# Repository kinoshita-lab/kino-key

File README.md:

# Kino-Key25

[日本語](README.ja.md)

Open source piano-type keyboard MIDI controller project

## Features

- All mechanical parts are easy 3D-printable. You can also easly order to 3D printing manufactures, such as JLC3dP, etc. (we may sell mech parts in the future, but not planned)
- Software is implemented on small, cheap seeeduino xiao rp2040. Everything includes keyboard scanning is modifiable according to your preferences.
- Most of the components on the PCB is easy to buy(we may sell PCBA board for easier assembly in the future, but not planned)

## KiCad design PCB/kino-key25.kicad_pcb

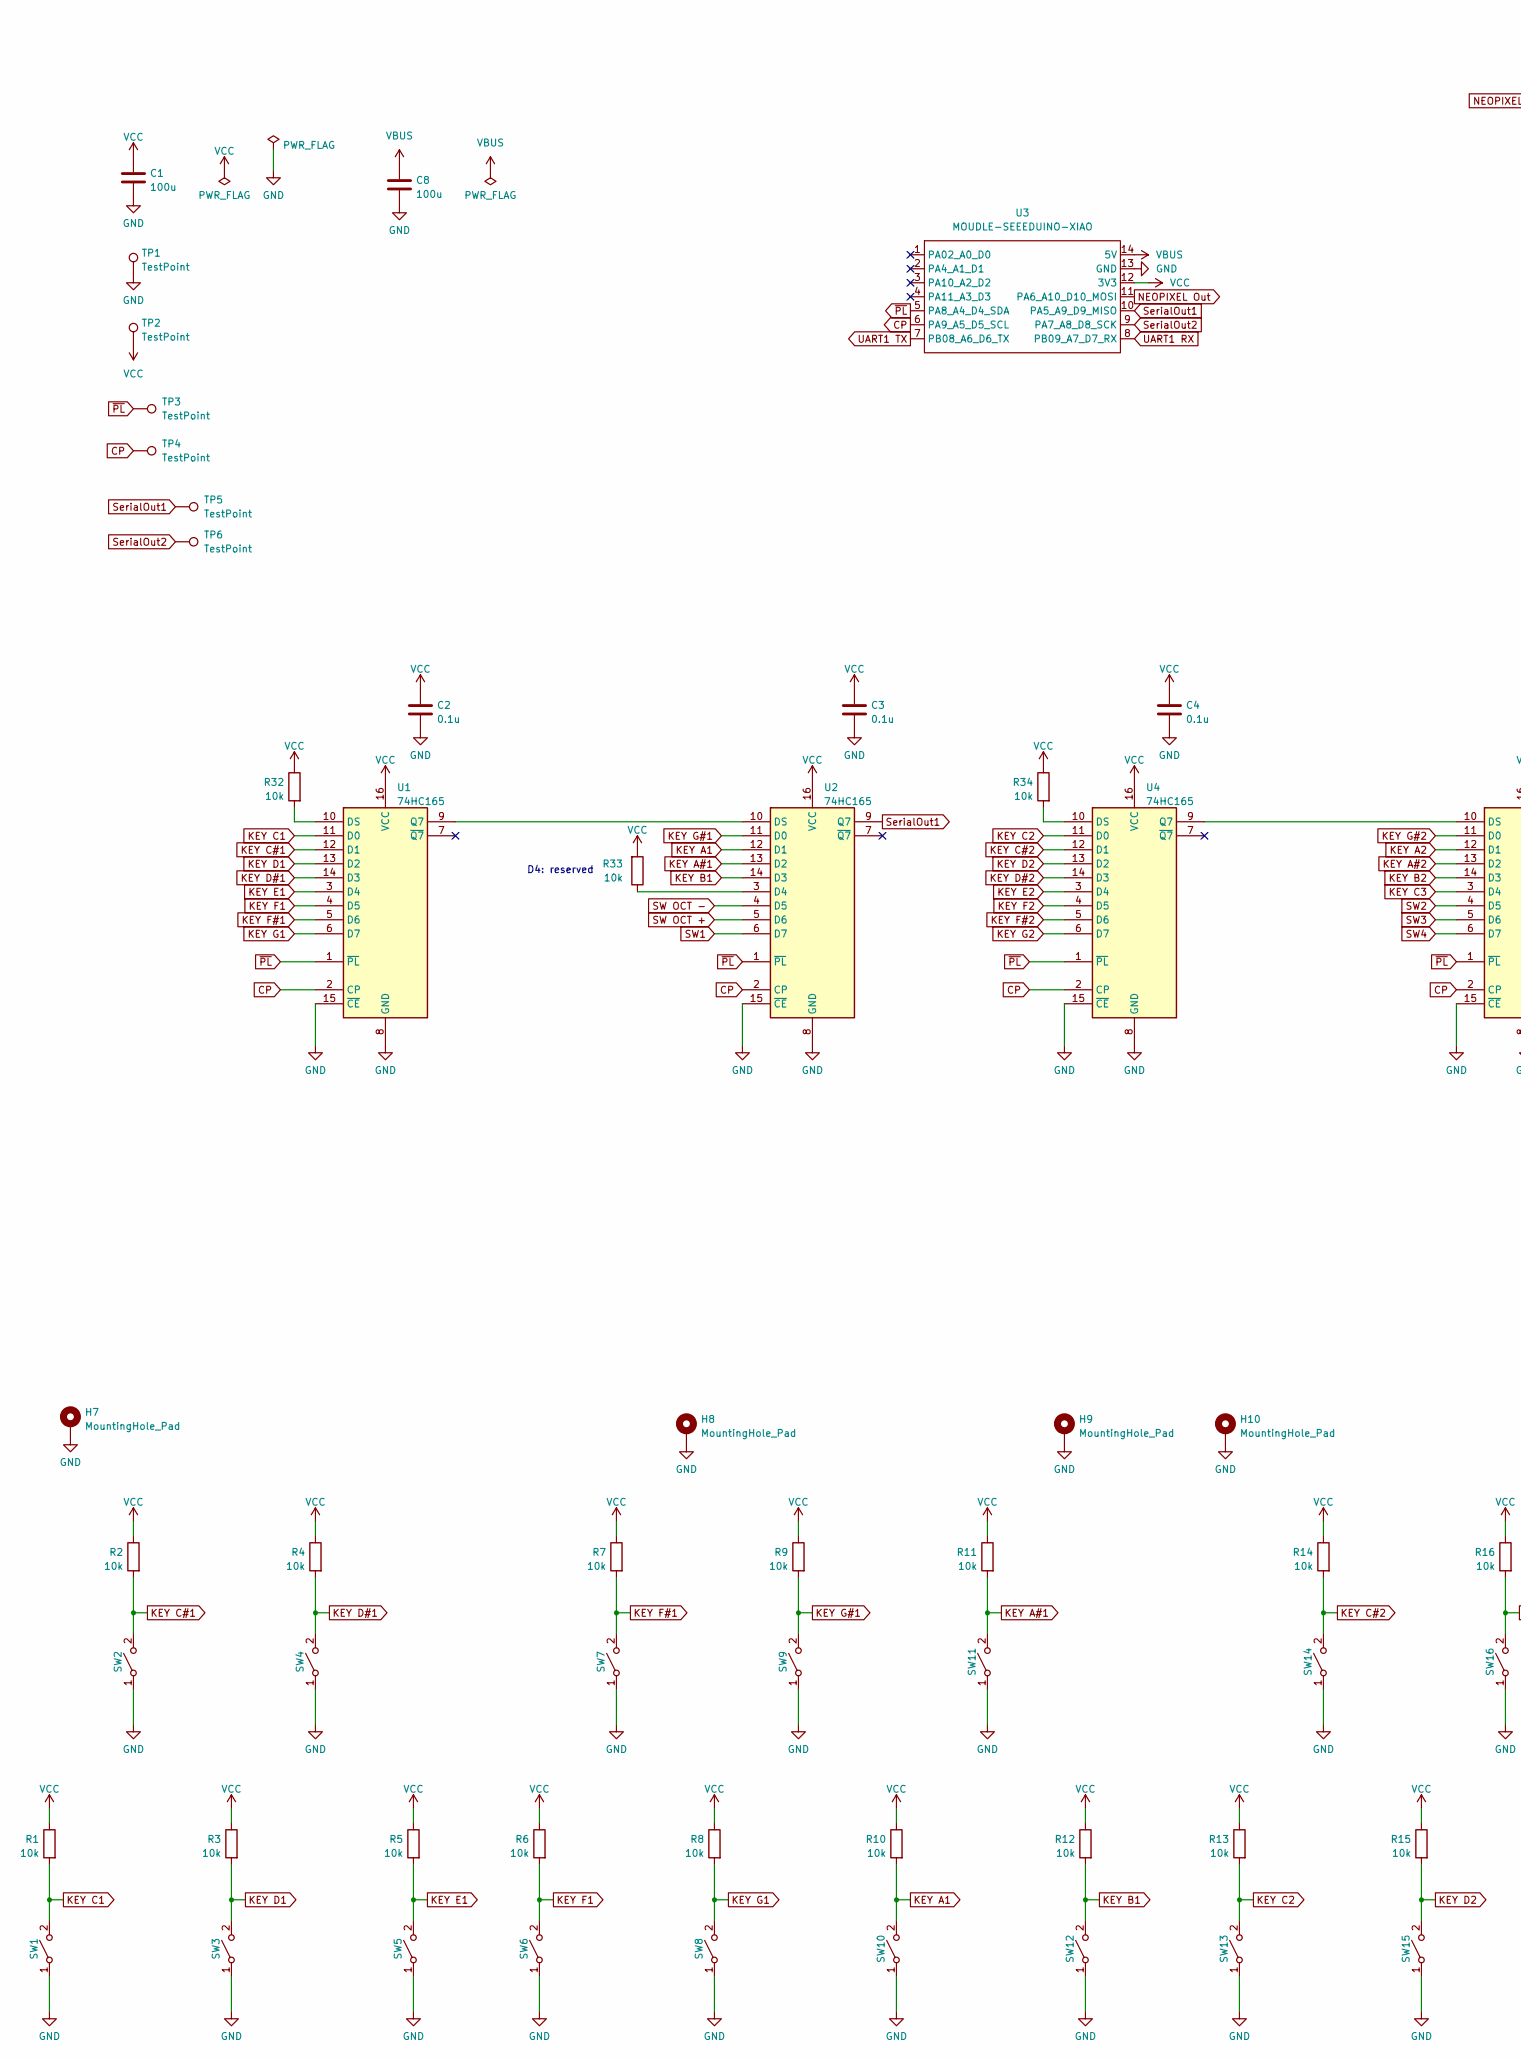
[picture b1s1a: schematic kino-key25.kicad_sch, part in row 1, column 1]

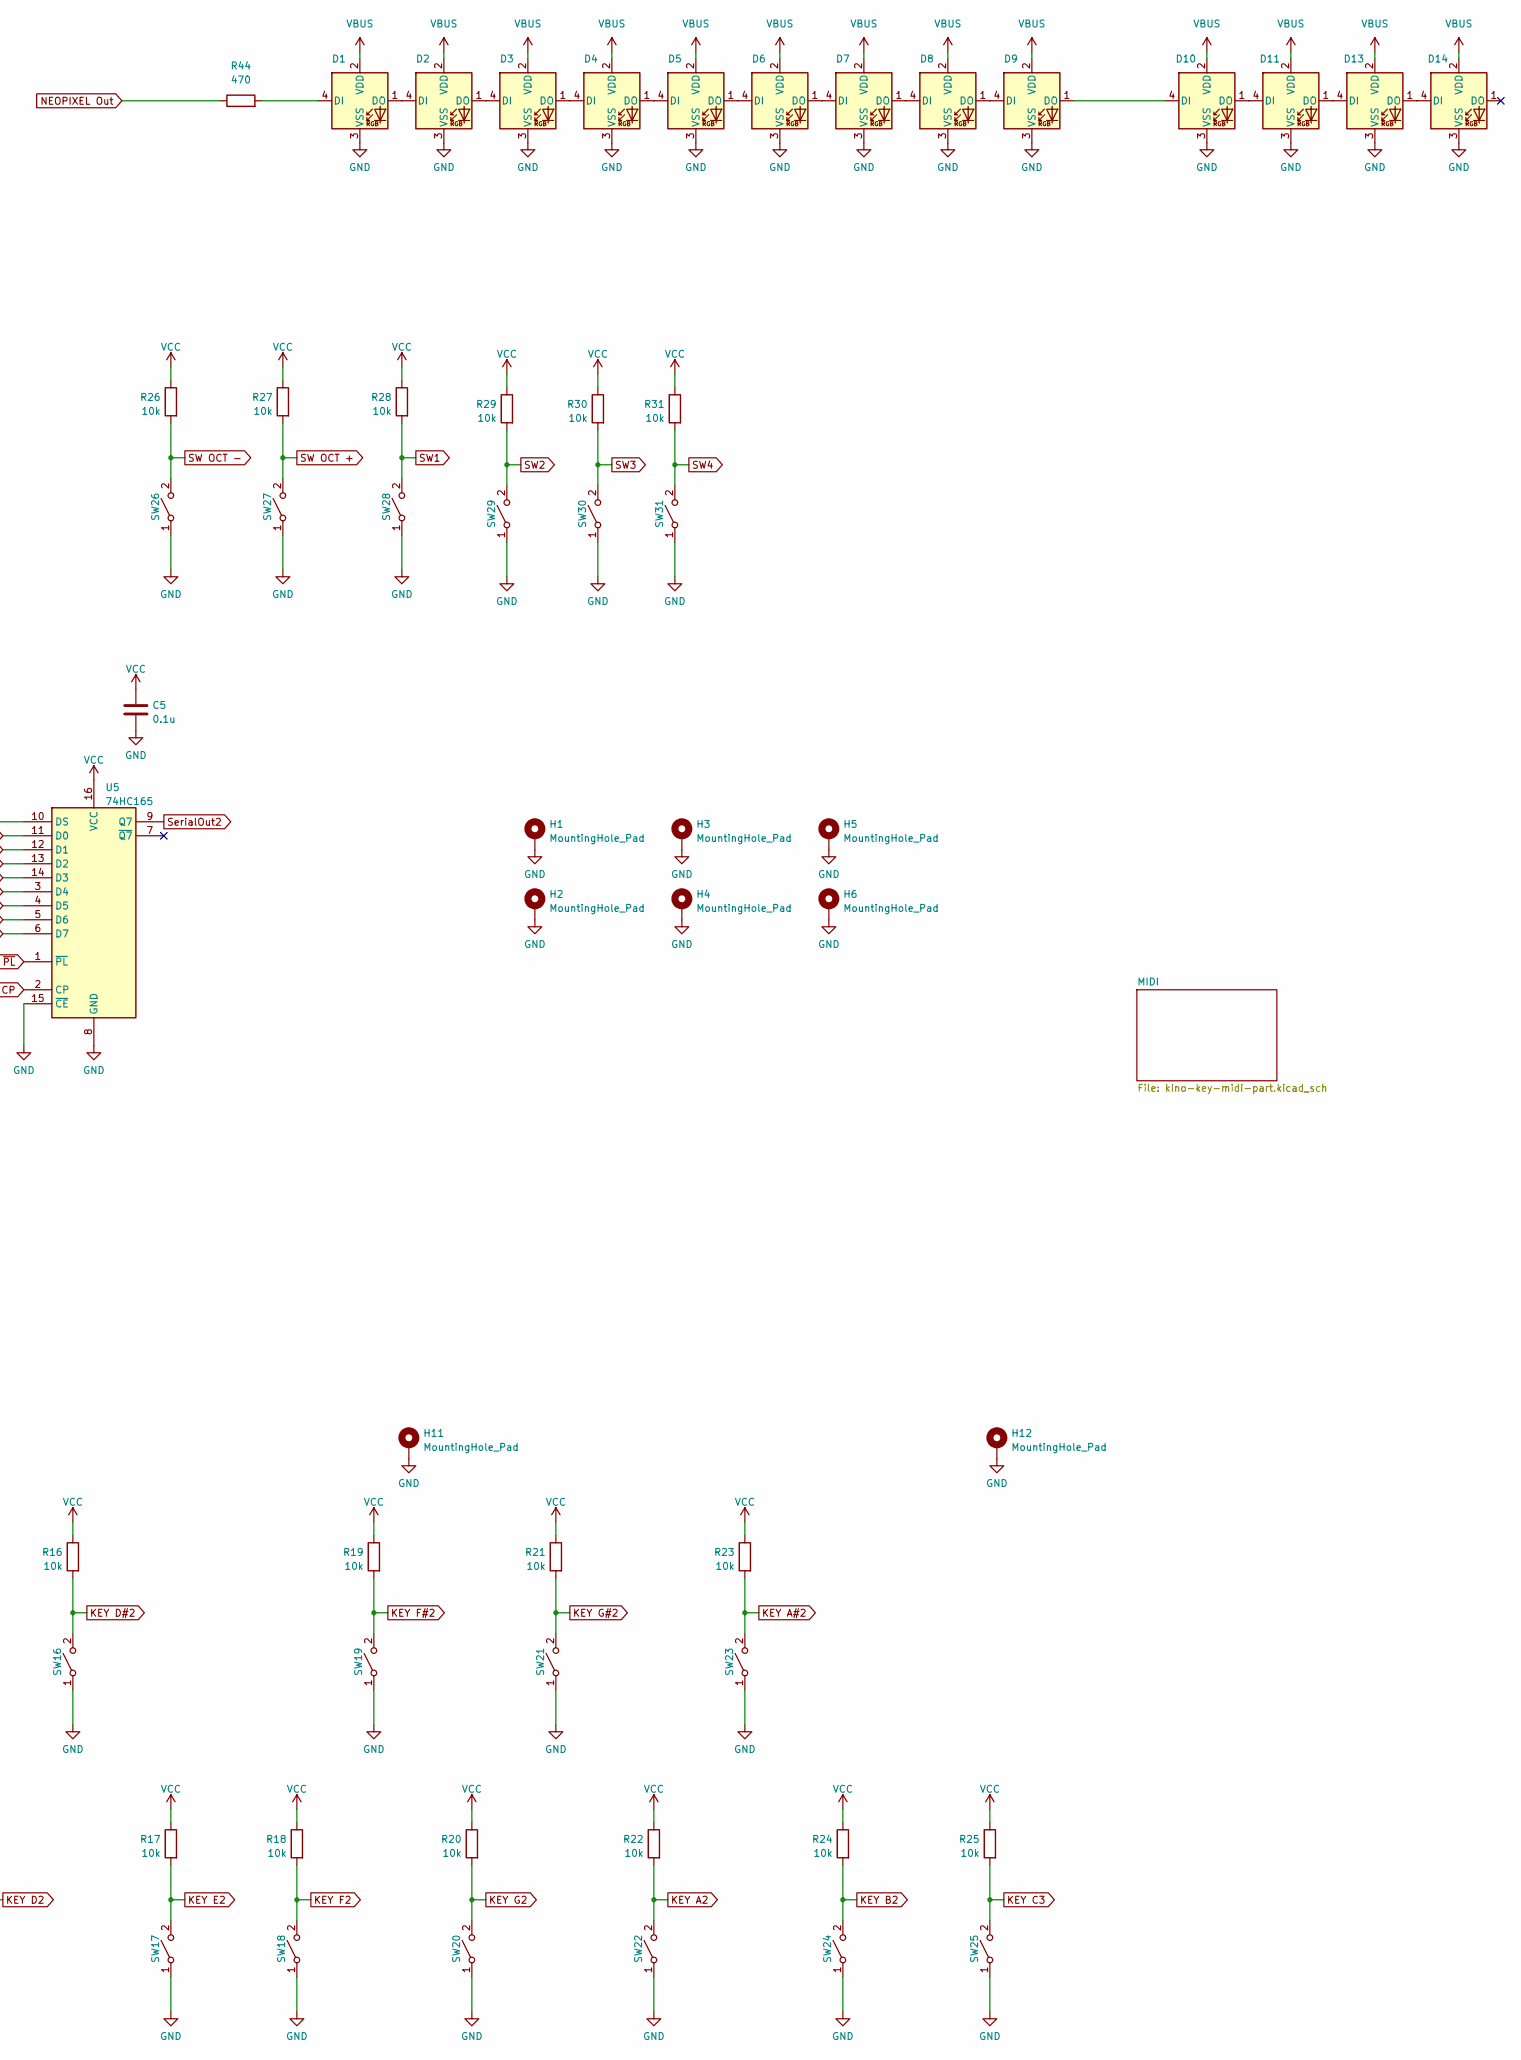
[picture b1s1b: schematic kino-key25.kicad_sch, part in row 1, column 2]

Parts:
C1, C8: 100u; C_1206_3216Metric_Pad1.33x1.80mm_HandSolder; LCSC C312983
C2, C3, C4, C5: 0.1u; C_0402_1005Metric_Pad0.74x0.62mm_HandSolder; LCSC C1525
D1, D2, D3, D4, D5, D6, D7, D8, D9, D10, D11, D13, D14: LED_NeoPixel_XL-1615RGBC-WS2812B; LCSC C5349954
H1, H2, H3, H4, H5, H6, H7, H8, H9, H10, H11, H12: MountingHole_Pad; MountingHole_3.2mm_M3_DIN965_Pad
R1, R2, R3, R4, R5, R6, R7, R8, R9, R10, R11, R12, R13, R14, R15, R16, R17, R18, R19, R20, R21, R22, R23, R24, R25, R26, R27, R28, R29, R30, R31, R32, R33, R34: 10k; R_0402_1005Metric_Pad0.72x0.64mm_HandSolder; LCSC C25744
R44: 470; R_0603_1608Metric; LCSC C23179
SW1, SW2, SW3, SW4, SW5, SW6, SW7, SW8, SW9, SW10, SW11, SW12, SW13, SW14, SW15, SW16, SW17, SW18, SW19, SW20, SW21, SW22, SW23, SW24, SW25, SW26, SW27, SW28, SW29, SW30, SW31: SW_SPST; SW_Tactile_6mm_x_6mm_Futsuuno_SMD; LCSC C294566
TP1, TP2, TP3, TP4, TP5, TP6: TestPoint; TestPoint_THTPad_D2.0mm_Drill1.0mm
U1, U2, U4, U5: 74HC165; TSSOP-16_4.4x5mm_P0.65mm; LCSC C80696
U3: MOUDLE-SEEEDUINO-XIAO; Seeduino_Xiao_RP2040_MOUDLE14P-2.54-21X17.8MM

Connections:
CP: TP4.1, U1.2 (CP), U2.2 (CP), U3.6 (PA9_A5_D5_SCL), U4.2 (CP), U5.2 (CP)
GND: C1.2, C2.2, C3.2, C4.2, C5.2, C8.2, D1.3 (VSS), D2.3 (VSS), D3.3 (VSS), D4.3 (VSS), D5.3 (VSS), D6.3 (VSS), D7.3 (VSS), D8.3 (VSS), D9.3 (VSS), D10.3 (VSS), D11.3 (VSS), D13.3 (VSS), D14.3 (VSS), H1.1, H2.1, H3.1, H4.1, H5.1, H6.1, H7.1, H8.1, H9.1, H10.1, H11.1, H12.1, SW1.1 (A), SW2.1 (A), SW3.1 (A), SW4.1 (A), SW5.1 (A), SW6.1 (A), SW7.1 (A), SW8.1 (A), SW9.1 (A), SW10.1 (A), SW11.1 (A), SW12.1 (A), SW13.1 (A), SW14.1 (A), SW15.1 (A), SW16.1 (A), SW17.1 (A), SW18.1 (A), SW19.1 (A), SW20.1 (A), SW21.1 (A), SW22.1 (A), SW23.1 (A), SW24.1 (A), SW25.1 (A), SW26.1 (A), SW27.1 (A), SW28.1 (A), SW29.1 (A), SW30.1 (A), SW31.1 (A), TP1.1, U1.8 (GND), U1.15 (~CE), U2.8 (GND), U2.15 (~CE), U3.13 (GND), U4.8 (GND), U4.15 (~CE), U5.8 (GND), U5.15 (~CE); also elsewhere on the board
KEY A1: R10.2, SW10.2 (B), U2.12 (D1)
KEY A2: R22.2, SW22.2 (B), U5.12 (D1)
KEY A#1: R11.2, SW11.2 (B), U2.13 (D2)
KEY A#2: R23.2, SW23.2 (B), U5.13 (D2)
KEY B1: R12.2, SW12.2 (B), U2.14 (D3)
KEY B2: R24.2, SW24.2 (B), U5.14 (D3)
KEY C1: R1.2, SW1.2 (B), U1.11 (D0)
KEY C2: R13.2, SW13.2 (B), U4.11 (D0)
KEY C3: R25.2, SW25.2 (B), U5.3 (D4)
KEY C#1: R2.2, SW2.2 (B), U1.12 (D1)
KEY C#2: R14.2, SW14.2 (B), U4.12 (D1)
KEY D1: R3.2, SW3.2 (B), U1.13 (D2)
KEY D2: R15.2, SW15.2 (B), U4.13 (D2)
KEY D#1: R4.2, SW4.2 (B), U1.14 (D3)
KEY D#2: R16.2, SW16.2 (B), U4.14 (D3)
KEY E1: R5.2, SW5.2 (B), U1.3 (D4)
KEY E2: R17.2, SW17.2 (B), U4.3 (D4)
KEY F1: R6.2, SW6.2 (B), U1.4 (D5)
KEY F2: R18.2, SW18.2 (B), U4.4 (D5)
KEY F#1: R7.2, SW7.2 (B), U1.5 (D6)
KEY F#2: R19.2, SW19.2 (B), U4.5 (D6)
KEY G1: R8.2, SW8.2 (B), U1.6 (D7)
KEY G2: R20.2, SW20.2 (B), U4.6 (D7)
KEY G#1: R9.2, SW9.2 (B), U2.11 (D0)
KEY G#2: R21.2, SW21.2 (B), U5.11 (D0)
NEOPIXEL Out: R44.1, U3.11 (PA6_A10_D10_MOSI)
unnamed: D1.4 (DI), R44.2
unnamed: D1.1 (DO), D2.4 (DI)
unnamed: D2.1 (DO), D3.4 (DI)
unnamed: D3.1 (DO), D4.4 (DI)
unnamed: D4.1 (DO), D5.4 (DI)
unnamed: D5.1 (DO), D6.4 (DI)
unnamed: D6.1 (DO), D7.4 (DI)
unnamed: D7.1 (DO), D8.4 (DI)
unnamed: D8.1 (DO), D9.4 (DI)
unnamed: D9.1 (DO), D10.4 (DI)
unnamed: D10.1 (DO), D11.4 (DI)
unnamed: D11.1 (DO), D13.4 (DI)
unnamed: D13.1 (DO), D14.4 (DI)
unnamed: R32.2, U1.10 (DS)
unnamed: U1.9 (Q7), U2.10 (DS)
unnamed: R33.1, U2.3 (D4)
unnamed: R34.2, U4.10 (DS)
unnamed: U4.9 (Q7), U5.10 (DS)
SW1: R28.2, SW28.2 (B), U2.6 (D7)
SW2: R29.2, SW29.2 (B), U5.4 (D5)
SW3: R30.2, SW30.2 (B), U5.5 (D6)
SW4: R31.2, SW31.2 (B), U5.6 (D7)
SW OCT +: R27.2, SW27.2 (B), U2.5 (D6)
SW OCT -: R26.2, SW26.2 (B), U2.4 (D5)
SerialOut1: TP5.1, U2.9 (Q7), U3.10 (PA5_A9_D9_MISO)
SerialOut2: TP6.1, U3.9 (PA7_A8_D8_SCK), U5.9 (Q7)
UART1 RX: U3.8 (PB09_A7_D7_RX); also elsewhere on the board
UART1 TX: U3.7 (PB08_A6_D6_TX); also elsewhere on the board
VBUS: C8.1, D1.2 (VDD), D2.2 (VDD), D3.2 (VDD), D4.2 (VDD), D5.2 (VDD), D6.2 (VDD), D7.2 (VDD), D8.2 (VDD), D9.2 (VDD), D10.2 (VDD), D11.2 (VDD), D13.2 (VDD), D14.2 (VDD), U3.14 (5V)
VCC: C1.1, C2.1, C3.1, C4.1, C5.1, R1.1, R2.1, R3.1, R4.1, R5.1, R6.1, R7.1, R8.1, R9.1, R10.1, R11.1, R12.1, R13.1, R14.1, R15.1, R16.1, R17.1, R18.1, R19.1, R20.1, R21.1, R22.1, R23.1, R24.1, R25.1, R26.1, R27.1, R28.1, R29.1, R30.1, R31.1, R32.1, R33.2, R34.1, TP2.1, U1.16 (VCC), U2.16 (VCC), U3.12 (3V3), U4.16 (VCC), U5.16 (VCC); also elsewhere on the board
~PL: TP3.1, U1.1 (~PL), U2.1 (~PL), U3.5 (PA8_A4_D4_SDA), U4.1 (~PL), U5.1 (~PL)

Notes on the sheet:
D4: reserved

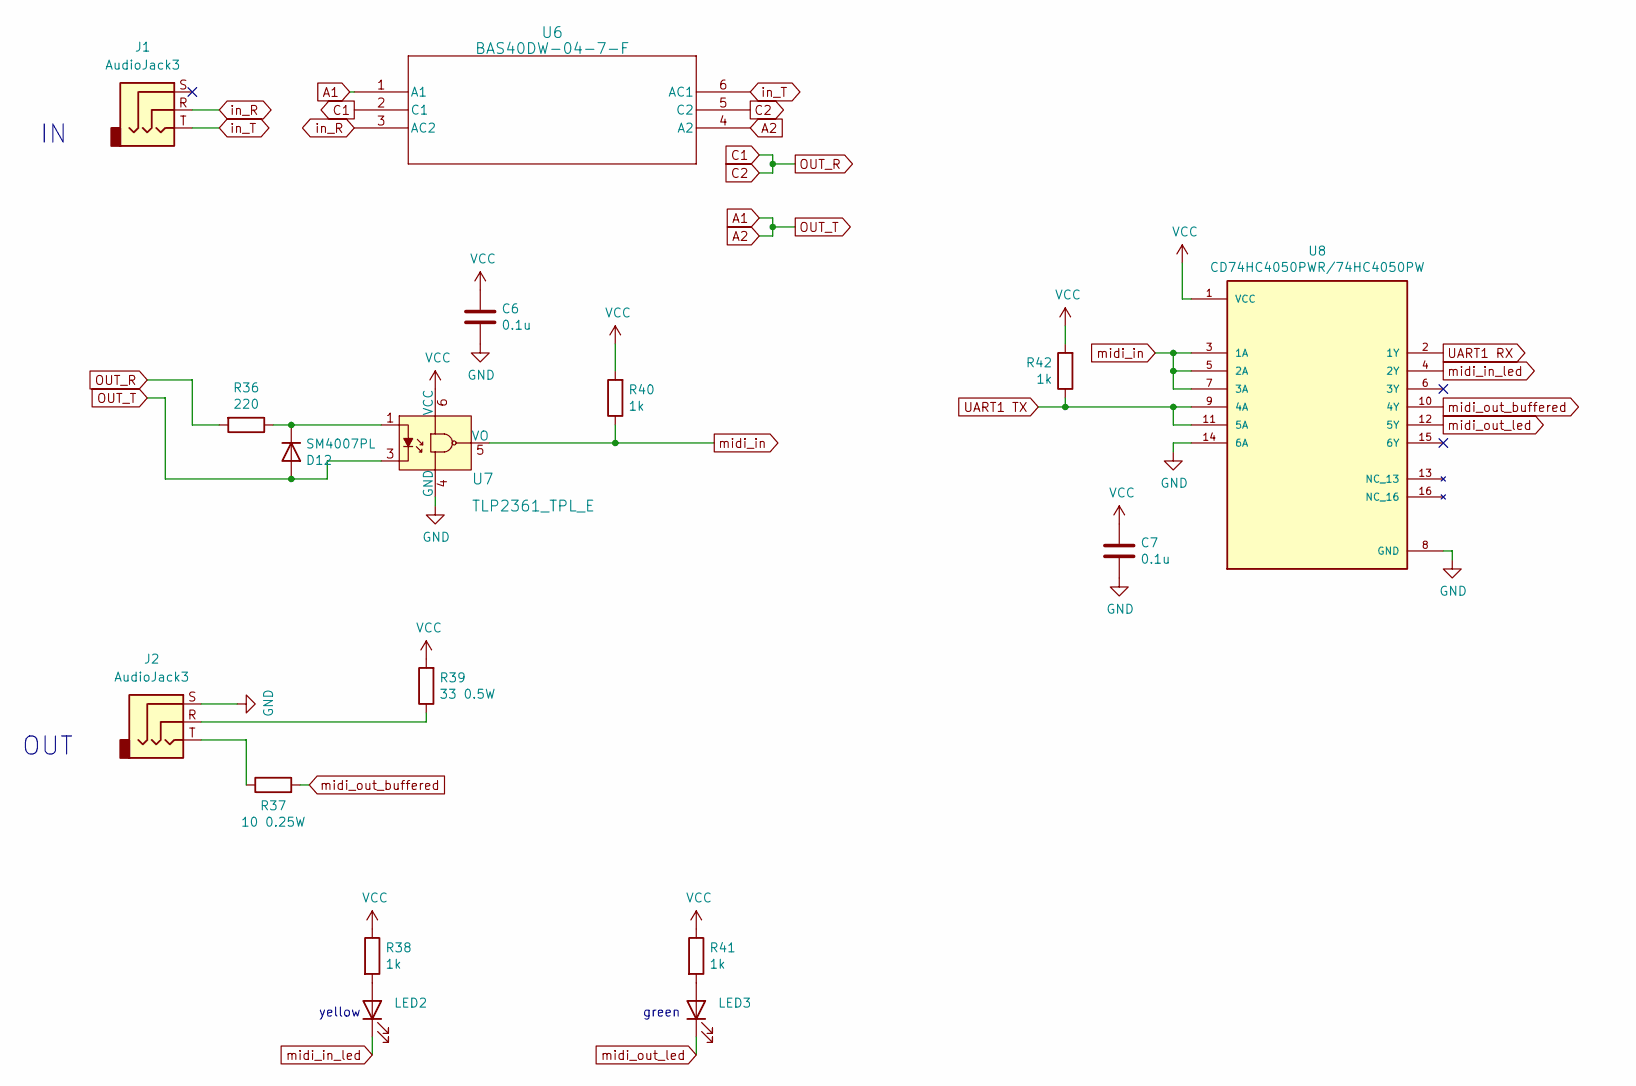
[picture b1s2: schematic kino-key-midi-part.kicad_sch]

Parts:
C6, C7: 0.1u; C_0603_1608Metric_Pad1.08x0.95mm_HandSolder; LCSC C14663
D12: SM4007PL; D_SOD-123; LCSC C64898
J1, J2: AudioJack3; 3.5mm_Stereo_TRS_PJ-3210-4A_and_ST-005-G
LED2: 19-213/Y2C-CQ2R2L/3T(CY); LED_0603_1608Metric_Pad1.05x0.95mm_HandSolder; LCSC C72038
LED3: 19-217/GHC-YR1S2/3T; LED_0603_1608Metric_Pad1.05x0.95mm_HandSolder; LCSC C2994781
R36: 220; R_1206_3216Metric_Pad1.30x1.75mm_HandSolder; LCSC C17957
R37: 10 0.25W; R_1206_3216Metric_Pad1.30x1.75mm_HandSolder; LCSC C17903
R38, R40, R41, R42: 1k; R_0603_1608Metric; LCSC C21190
R39: 33 0.5W; R_1210_3225Metric_Pad1.30x2.65mm_HandSolder; LCSC C407192
U6: BAS40DW-04-7-F; SOT-363_DIO; LCSC C134364
U7: TLP2361_TPL_E; SO-5_4.4x3.6mm_P1.27mm; MPN TLP2361(TPL,E; Digi-Key_PN TLP2361(TPLECT-ND
U8: CD74HC4050PWR/74HC4050PW; SOP65P640X120-16N; PARTREV February 2005; LCSC C546991

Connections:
A1: D12.2 (A), U6.1 (A1), U6.4 (A2), U7.3
C1: R36.2, U6.2 (C1), U6.5 (C2)
GND: C6.2, C7.2, J2.S, U7.4 (GND), U8.8 (GND), U8.14 (6A); also elsewhere on the board
unnamed: D12.1 (K), R36.1, U7.1
unnamed: J2.R, R39.1
unnamed: J2.T, R37.1
unnamed: LED2.2 (A), R38.2
unnamed: LED3.2 (A), R41.2
UART1 RX: U8.2 (1Y); also elsewhere on the board
UART1 TX: R42.1, U8.9 (4A), U8.11 (5A); also elsewhere on the board
VCC: C6.1, C7.1, R38.1, R39.2, R40.2, R41.1, R42.2, U7.6 (VCC), U8.1 (VCC); also elsewhere on the board
in_R: J1.R, U6.3 (AC2)
in_T: J1.T, U6.6 (AC1)
midi_in: R40.1, U7.5 (VO), U8.3 (1A), U8.5 (2A), U8.7 (3A)
midi_in_led: LED2.1 (K), U8.4 (2Y)
midi_out_buffered: R37.2, U8.10 (4Y)
midi_out_led: LED3.1 (K), U8.12 (5Y)

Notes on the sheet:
green
OUT
yellow

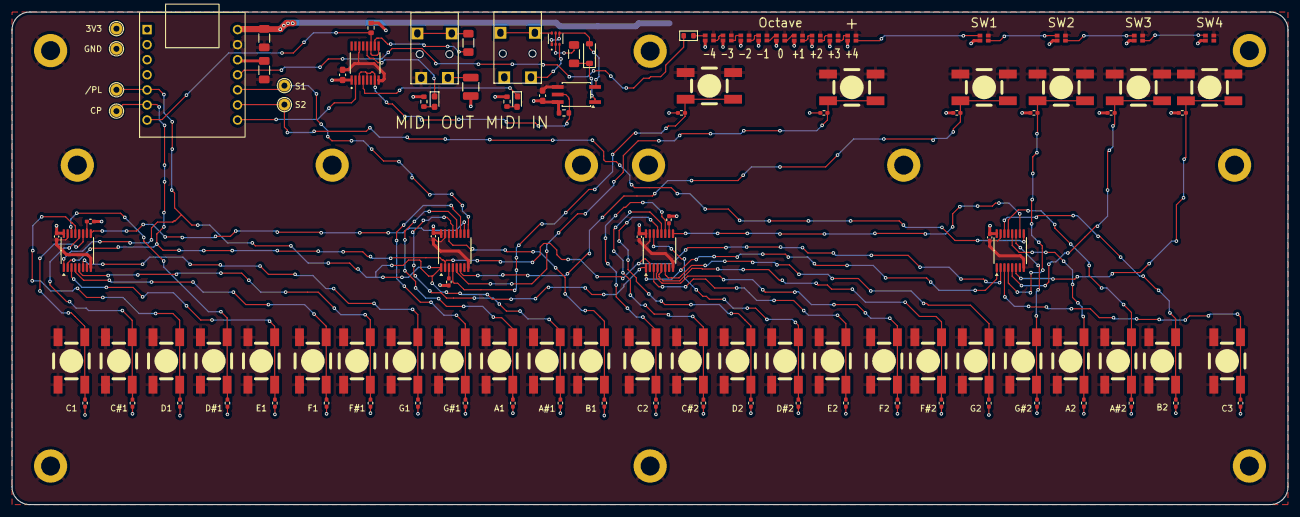
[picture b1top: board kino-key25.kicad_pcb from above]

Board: 2 copper layers, 215.0 x 83.0 mm, 125 parts (0 on the bottom side), 72 nets.

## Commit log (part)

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2024-09-01 [mech] Add FreeCAD and exported stl files
2024-09-17 add mech design
2024-09-17 Add rest of files
2024-09-17 tweak README
2024-09-17 Create LICENSE
2024-09-17 add pdf schematics
2025-02-27 [mech] Open and save with FreeCad 1.0
2025-02-27 [PCB] Update to KiCad 9.0, remove voltage conversion #6
2025-05-29 modify some
2025-09-21 Fixes #5
